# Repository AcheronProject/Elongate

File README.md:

# Acheron 50-SM-S-F072-MX-TH-WI (Codename "Elongate")

See [this page](https://gondolindrim.github.io/AcheronDocs/elongate/intro.html) for the ElongatePCB documentation.

## Supported layouts

Click [this link](http://www.keyboard-layout-editor.com/#/gists/a7ea70bf0b0dbade28f4dd3f8dd61796) for the KLE file for Elongate.

## Renders

Click at the images to zoom in.

Renders generated by the [tracespace.io](https://tracespace.io/view/) site.

## Copyright notice

This project is released under the Acheron Open-Hardware License V1.3. For the license, please refer to the LICENCE.md file.

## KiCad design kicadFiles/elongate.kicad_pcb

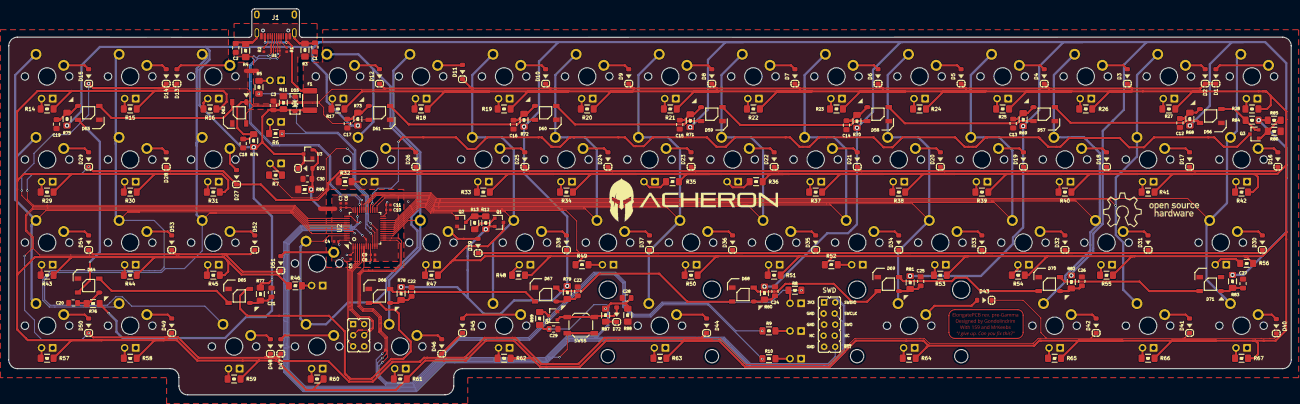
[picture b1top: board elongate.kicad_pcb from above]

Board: 2 copper layers, 294.0 x 88.5 mm, 324 parts (1 on the bottom side), 198 nets.

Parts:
C1, C2: 100n; C_0805_2012Metric_Pad1.15x1.40mm_HandSolder
C3, C12, C13, C14, C15, C16, C17, C18, C19, C20, C21, C22, C23, C24, C25, C26, C27, C30: 1u; C_0805_2012Metric_Pad1.15x1.40mm_HandSolder
C4, C5, C6, C10: 100n; C_0402_1005Metric
C7, C11: 4.7u; C_0402_1005Metric
C8: 1u; C_0402_1005Metric
C9: 10n; C_0402_1005Metric
C28: 100u; C_0805_2012Metric_Pad1.15x1.40mm_HandSolder
C29: 10u; C_0805_2012Metric_Pad1.15x1.40mm_HandSolder
D1, D2, D3, D4, D5, D6, D7, D8, D9, D10, D11, D12, D13, D14, D15, D16, D17, D18, D19, D20, D21, D22, D23, D24, D25, D26, D27, D28, D29, D30, D31, D32, D33, D34, D35, D36, D37, D38, D39, D40, D41, D42, D43, D44, D45, D46, D47, D48, D49, D50, D51, D52, D53, D54, D72: 1N4148; D_SOD-123
D55: SMF9.0CA; D_SOD-123_Bidirectional
D56, D57, D58, D59, D60, D61, D62, D63, D64, D65, D66, D67, D68, D69, D70, D71: WS2812C; LED_WS2812B_5.0x5.0mm_P3.2mm
D73: RB060M-60TR; D_SOD-123
F1: RF1338-000; Fuse_1812_4532Metric_Pad1.30x3.40mm_HandSolder
J1: TYPE-C-31-M12_13; TYPE-C-31-M-12
J2: Conn_ARM_JTAG_SWD_10
J3: Conn_01x6; PinHeader_2x3_P2.54mm_Vertical
L1: AcheronLogo; acheronLong
L2: ElongateLogoPlated; elongateLogo
L3: ElongateLabel; elongateLabel
L4: OSHLogo; osh-logo
L5: BRFlag; brazilFlag
LED1, LED2, LED3, LED4, LED5, LED6, LED7, LED8, LED9, LED10, LED11, LED12, LED13, LED14, LED15, LED16, LED17, LED18, LED19, LED20, LED21, LED22, LED23, LED24, LED25, LED26, LED27, LED28, LED29, LED30, LED31, LED32, LED33, LED34, LED35, LED36, LED37, LED38, LED39, LED40, LED41, LED42, LED43, LED44, LED45, LED46, LED47, LED48, LED49, LED50, LED51, LED52, LED53, LED54, LED55, LED56, LED57, LED58, LED59, LED60: LED; LED_THT_2.54mm
Q1, Q3: AO3401A; SOT-23
Q2, Q4: DTC123JKAT146; SOT-23
R1, R2: 5.1k; R_0402_1005Metric
R3, R4: 1M; R_SMD_1206
R5, R6, R7, R8, R9, R10, R14, R15, R16, R17, R18, R19, R20, R21, R22, R23, R24, R25, R26, R27, R28, R29, R30, R31, R32, R33, R34, R35, R36, R37, R38, R39, R40, R41, R42, R43, R44, R45, R46, R47, R48, R49, R50, R51, R52, R53, R54, R55, R56, R57, R58, R59, R60, R61, R62, R63, R64, R65, R66, R67: 390R; R_SMD_1206
R11, R88, R90: 100k; R_SMD_1206
R12, R84, R86: 10k; R_SMD_1206
R13, R89: 100R; R_SMD_1206
R68, R69, R70, R71, R72, R73, R74, R75, R76, R77, R78, R79, R80, R81, R82, R83: 3R; R_SMD_1206
R85: 5.1k; R_SMD_1206
R87: 33k; R_SMD_1206
SW1, SW2, SW3, SW4, SW5, SW6, SW7, SW8, SW9, SW10, SW11, SW12, SW13, SW14, SW15, SW17, SW18, SW19, SW20, SW21, SW22, SW23, SW24, SW25, SW27, SW28, SW29, SW31, SW32, SW33, SW34, SW35, SW36, SW37, SW38, SW41, SW45, SW46, SW47, SW48, SW49, SW50, SW51, SW52, SW53, SW54: MXSwitch; MX100
SW16, SW39, SW40, SW42: MXSwitch; MX125
SW26, SW30: MXSwitch; MX175
SW43: MXSwitch; MX225R
SW44: MXSwitch; MX275R
SW55: K2-1187SQ-A4SW-06; smdPushBtn
U1: TPD4E05U06DQAR; USON-10_2.5x1.0mm_P0.5mm
U2: STM32F072CBT6; LQFP-48_7x7mm_P0.5mm
U3: MCP1700-3302E; SOT-23

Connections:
3V3: C4.2, C5.1, C6.1, C7.1, C8.2, C9.2, C10.1, C11.1, C30.2, D73.2 (A), J2.1 (VTref), J3.5, R90.1, SW55.1, U2.1 (VBAT), U2.9 (VDDA), U2.24 (VDD), U2.36 (VDDIO2), U2.48 (VDD), U3.2 (VO)
5V: C3.1, D55.2 (A2), D73.1 (K), F1.2, Q1.2 (S), R11.2, R12.1, R68.1, R69.1, R70.1, R71.1, R72.1, R73.1, R74.1, R75.1, R76.1, R77.1, R78.1, R79.1, R80.1, R81.1, R82.1, R83.1, R84.1, R85.1, U3.3 (VI)
/SHIELD: C1.1, C2.1, J1.S (SHIELD), R3.2, R4.2
BOOT0: C28.2, R87.1, R88.1, U2.44 (BOOT0)
Col1: SW1.1 (Col), SW16.1 (Col), SW30.1 (Col), SW40.1 (Col), U2.31 (TIM1_CH3/PA10)
Col2: SW2.1 (Col), SW17.1 (Col), SW41.1 (Col), U2.30 (TIM1_CH2/PA9)
Col3: SW3.1 (Col), SW18.1 (Col), SW31.1 (Col), SW42.1 (Col), U2.29 (TIM1_CH1/PA8)
Col4: SW4.1 (Col), SW19.1 (Col), SW32.1 (Col), U2.27 (PB14/SPI2_MISO/I2S2_MCK/I2C2_SDA/TIM15_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)
Col5: SW5.1 (Col), SW20.1 (Col), SW33.1 (Col), SW43.1 (Col), U2.25 (PB12)
Col6: SW6.1 (Col), SW21.1 (Col), SW34.1 (Col), U2.22 (PB11/TIM2_CH4/I2C2_SDA)
Col7: SW7.1 (Col), SW22.1 (Col), SW35.1 (Col), U2.21 (PB10/SPI2_SCK/I2C2_SCL/TIM2_CH3)
Col8: SW8.1 (Col), SW23.1 (Col), SW36.1 (Col), SW44.1 (Col), U2.20 (PB2)
Col9: SW9.1 (Col), SW24.1 (Col), SW37.1 (Col), U2.19 (PB1/TIM3_CH4/TIM14_CH1/ADC_IN9)
Col10: SW10.1 (Col), SW25.1 (Col), SW38.1 (Col), SW45.1 (Col), U2.17 (PA7/TIM3_CH2/TIM14_CH1/ADC_IN7)
Col11: SW11.1 (Col), SW39.1 (Col), SW46.1 (Col), U2.15 (PA5/ADC_IN5/DAC_OUT2)
Col12: SW12.1 (Col), SW26.1 (Col), SW47.1 (Col), SW51.1 (Col), U2.46 (SPI2_NSS/I2S2_WS/I2C1_SDA/TIM17_CH1/PB9)
Col13: SW13.1 (Col), SW27.1 (Col), SW48.1 (Col), SW52.1 (Col), U2.45 (I2C1_SCL/TIM16_CH1/PB8)
Col14: SW14.1 (Col), SW28.1 (Col), SW49.1 (Col), SW53.1 (Col), U2.43 (2C1_SDA/PB7)
Col15: SW15.1 (Col), SW29.1 (Col), SW50.1 (Col), SW54.1 (Col), U2.42 (I2C1_SCL/PB6)
D+: J1.A6 (D+), J1.B6 (D+), U1.2 (IO2), U1.5 (D2-), U1.6 (NC), U1.9 (NC), U2.33 (USB_DP/PA12)
D-: J1.A7 (D-), J1.B7 (D-), U1.1 (IO1), U1.4 (D2+), U1.7 (NC), U1.10 (NC), U2.32 (USB_DM/TIM1_CH4/PA11)
EXTRA_1: J3.1, U2.2 (PC13)
EXTRA_2: J3.2, U2.3 (PC14/OSC32_IN)
EXTRA_3: J3.3, U2.4 (PC15/OSC32_OUT)
EXTRA_4: J3.4, U2.5 (PF0/OSC_IN)
GND: C1.2, C2.2, C3.2, C4.1, C5.2, C6.2, C7.2, C8.1, C9.1, C10.2, C11.2, C12.2, C13.2, C14.2, C15.2, C16.2, C17.2, C18.2, C19.2, C20.2, C21.2, C22.2, C23.2, C24.2, C25.2, C26.2, C27.2, C28.1, C29.1, C30.1, D55.1 (A1), D56.3 (VSS), D57.3 (VSS), D58.3 (VSS), D59.3 (VSS), D60.3 (VSS), D61.3 (VSS), D62.3 (VSS), D63.3 (VSS), D64.3 (VSS), D65.3 (VSS), D66.3 (VSS), D67.3 (VSS), D68.3 (VSS), D69.3 (VSS), D70.3 (VSS), D71.3 (VSS), J1.A1 (GND), J1.B1 (GND), J2.3 (GND), J2.5 (GND), J2.9 (GNDDetect), J3.6, LED1.K, LED2.K, LED3.K, LED4.K, LED5.K, LED6.K, LED7.K, LED8.K, LED9.K, LED10.K, LED11.K, LED12.K, LED13.K, LED14.K, LED15.K, LED16.K, LED17.K, LED18.K, LED19.K, LED20.K, LED21.K, LED22.K, LED23.K, LED24.K, LED25.K, LED26.K, LED27.K, LED28.K, LED29.K, LED30.K, LED31.K, LED32.K, LED33.K, LED34.K, LED35.K, LED36.K, LED37.K, LED38.K, LED39.K, LED40.K, LED41.K, LED42.K, LED43.K, LED44.K, LED45.K, LED46.K, LED47.K, LED48.K, LED49.K, LED50.K, LED51.K, LED52.K, LED53.K, LED54.K, LED55.K, LED56.K, LED57.K, LED58.K, LED59.K, LED60.K, Q2.2 (E), Q4.2 (E), R1.1, R2.1, R3.1, R4.1, R11.1, R86.2, R88.2, R90.2, U1.3 (GND), U1.8 (GND), U2.8 (VSSA), U2.23 (VSS), U2.35 (VSS), U2.47 (VSS), U3.1 (GND)
INDICATOR1: R5.1, U2.12 (PA2/ADC_IN2)
INDICATOR2: R6.1, U2.11 (PA1/ADC_IN1)
INDICATOR3: R7.1, U2.10 (PA0/ADC_IN0)
INDICATOR4: R8.1, U2.14 (PA4/TIM14_CH1/ADC_IN4)
INDICATOR5: R9.1, U2.13 (PA3/TIM15_CH2/ADC_IN3)
INDICATOR6: R10.1, U2.6 (PF1/OSC_OUT)
LED_PWM: Q2.1 (B), U2.16 (PA6/ADC_IN6/TIM3_CH1/TIM16_CH1)
unnamed: C12.1, D56.1 (VDD), R68.2
unnamed: C13.1, D57.1 (VDD), R69.2
unnamed: C14.1, D58.1 (VDD), R70.2
unnamed: C15.1, D59.1 (VDD), R71.2
unnamed: C16.1, D60.1 (VDD), R72.2
unnamed: C17.1, D61.1 (VDD), R73.2
unnamed: C18.1, D62.1 (VDD), R74.2
unnamed: C19.1, D63.1 (VDD), R75.2
unnamed: C20.1, D64.1 (VDD), R76.2
unnamed: C21.1, D65.1 (VDD), R77.2
unnamed: C22.1, D66.1 (VDD), R78.2
unnamed: C23.1, D67.1 (VDD), R79.2
unnamed: C24.1, D68.1 (VDD), R80.2
unnamed: C25.1, D69.1 (VDD), R81.2
unnamed: C26.1, D70.1 (VDD), R82.2
unnamed: C27.1, D71.1 (VDD), R83.2
unnamed: D1.2 (A), SW1.2 (Row)
unnamed: D2.2 (A), SW2.2 (Row)
unnamed: D3.2 (A), SW3.2 (Row)
unnamed: D4.2 (A), SW4.2 (Row)
unnamed: D5.2 (A), SW5.2 (Row)
unnamed: D6.2 (A), SW6.2 (Row)
unnamed: D7.2 (A), SW7.2 (Row)
unnamed: D8.2 (A), SW8.2 (Row)
unnamed: D9.2 (A), SW9.2 (Row)
unnamed: D10.2 (A), SW10.2 (Row)
unnamed: D11.2 (A), SW11.2 (Row)
unnamed: D12.2 (A), SW12.2 (Row)
unnamed: D13.2 (A), SW13.2 (Row)
unnamed: D14.2 (A), SW14.2 (Row)
unnamed: D15.2 (A), SW15.2 (Row)
unnamed: D16.2 (A), SW16.2 (Row)
unnamed: D17.2 (A), SW17.2 (Row)
unnamed: D18.2 (A), SW18.2 (Row)
unnamed: D19.2 (A), SW19.2 (Row)
unnamed: D20.2 (A), SW20.2 (Row)
unnamed: D21.2 (A), SW21.2 (Row)
unnamed: D22.2 (A), SW22.2 (Row)
unnamed: D23.2 (A), SW23.2 (Row)
unnamed: D24.2 (A), SW24.2 (Row)
unnamed: D25.2 (A), SW25.2 (Row)
unnamed: D26.2 (A), SW26.2 (Row)
unnamed: D27.2 (A), SW27.2 (Row)
unnamed: D28.2 (A), SW28.2 (Row)
unnamed: D29.2 (A), SW29.2 (Row)
unnamed: D30.2 (A), SW30.2 (Row)
unnamed: D31.2 (A), SW31.2 (Row)
unnamed: D32.2 (A), SW32.2 (Row)
unnamed: D33.2 (A), SW33.2 (Row)
unnamed: D34.2 (A), SW34.2 (Row)
unnamed: D35.2 (A), SW35.2 (Row)
unnamed: D36.2 (A), SW36.2 (Row)
unnamed: D37.2 (A), SW37.2 (Row)
unnamed: D38.2 (A), SW38.2 (Row)
unnamed: D39.2 (A), SW39.2 (Row)
unnamed: D40.2 (A), SW40.2 (Row)
unnamed: D41.2 (A), SW41.2 (Row)
unnamed: D42.2 (A), SW42.2 (Row)
unnamed: D43.2 (A), SW43.2 (Row)
unnamed: D44.2 (A), SW44.2 (Row)
unnamed: D45.2 (A), SW45.2 (Row)
unnamed: D46.2 (A), SW46.2 (Row)
unnamed: D47.2 (A), SW47.2 (Row)
unnamed: D48.2 (A), SW48.2 (Row)
unnamed: D49.2 (A), SW49.2 (Row)
unnamed: D50.2 (A), SW50.2 (Row)
unnamed: D51.2 (A), SW51.2 (Row)
unnamed: D52.2 (A), SW52.2 (Row)
unnamed: D53.2 (A), SW53.2 (Row)
unnamed: D54.2 (A), SW54.2 (Row)
unnamed: D56.2 (DOUT), D57.4 (DIN)
unnamed: D57.2 (DOUT), D58.4 (DIN)
unnamed: D58.2 (DOUT), D59.4 (DIN)
unnamed: D59.2 (DOUT), D60.4 (DIN)
unnamed: D60.2 (DOUT), D61.4 (DIN)
unnamed: D61.2 (DOUT), D62.4 (DIN)
unnamed: D62.2 (DOUT), D63.4 (DIN)
unnamed: D63.2 (DOUT), D64.4 (DIN)
unnamed: D64.2 (DOUT), D65.4 (DIN)
unnamed: D65.2 (DOUT), D66.4 (DIN)
unnamed: D66.2 (DOUT), D67.4 (DIN)
unnamed: D67.2 (DOUT), D68.4 (DIN)
unnamed: D68.2 (DOUT), D69.4 (DIN)
unnamed: D69.2 (DOUT), D70.4 (DIN)
unnamed: D70.2 (DOUT), D71.4 (DIN)
unnamed: D72.1 (K), R87.2
unnamed: D72.2 (A), Q4.1 (B), SW55.2
unnamed: J1.A5 (CC1), R1.2
unnamed: J1.B5 (CC2), R2.2
unnamed: LED1.A, R5.2
unnamed: LED2.A, R6.2
unnamed: LED3.A, R7.2
unnamed: LED4.A, R8.2
unnamed: LED5.A, R9.2
unnamed: LED6.A, R10.2
unnamed: LED7.A, R14.2
unnamed: LED8.A, R15.2
unnamed: LED9.A, R16.2
unnamed: LED10.A, R17.2
unnamed: LED11.A, R18.2
unnamed: LED12.A, R19.2
unnamed: LED13.A, R20.2
unnamed: LED14.A, R21.2
unnamed: LED15.A, R22.2
unnamed: LED16.A, R23.2
unnamed: LED17.A, R24.2
unnamed: LED18.A, R25.2
unnamed: LED19.A, R26.2
unnamed: LED20.A, R27.2
unnamed: LED21.A, R28.2
unnamed: LED22.A, R29.2
unnamed: LED23.A, R30.2
unnamed: LED24.A, R31.2
unnamed: LED25.A, R32.2
unnamed: LED26.A, R33.2
unnamed: LED27.A, R34.2
unnamed: LED28.A, R35.2
unnamed: LED29.A, R36.2
unnamed: LED30.A, R37.2
unnamed: LED31.A, R38.2
unnamed: LED32.A, R39.2
unnamed: LED33.A, R40.2
unnamed: LED34.A, R41.2
unnamed: LED35.A, R42.2
unnamed: LED36.A, R43.2
unnamed: LED37.A, R44.2
unnamed: LED38.A, R45.2
unnamed: LED39.A, R46.2
unnamed: LED40.A, R47.2
unnamed: LED41.A, R48.2
unnamed: LED42.A, R49.2
unnamed: LED43.A, R50.2
unnamed: LED44.A, R51.2
unnamed: LED45.A, R52.2
unnamed: LED46.A, R53.2
unnamed: LED47.A, R54.2
unnamed: LED48.A, R55.2
unnamed: LED49.A, R56.2
unnamed: LED50.A, R57.2
unnamed: LED51.A, R58.2
unnamed: LED52.A, R59.2
unnamed: LED53.A, R60.2
unnamed: LED54.A, R61.2
unnamed: LED55.A, R62.2
unnamed: LED56.A, R63.2
unnamed: LED57.A, R64.2
unnamed: LED58.A, R65.2
unnamed: LED59.A, R66.2
unnamed: LED60.A, R67.2
unnamed: Q1.1 (G), R13.1
unnamed: Q1.3 (D), R14.1, R15.1, R16.1, R17.1, R18.1, R19.1, R20.1, R21.1, R22.1, R23.1, R24.1, R25.1, R26.1, R27.1, R28.1, R29.1, R30.1, R31.1, R32.1, R33.1, R34.1, R35.1, R36.1, R37.1, R38.1, R39.1, R40.1, R41.1, R42.1, R43.1, R44.1, R45.1, R46.1, R47.1, R48.1, R49.1, R50.1, R51.1, R52.1, R53.1, R54.1, R55.1, R56.1, R57.1, R58.1, R59.1, R60.1, R61.1, R62.1, R63.1, R64.1, R65.1, R66.1, R67.1
unnamed: Q2.3 (C), R12.2, R13.2
unnamed: Q3.1 (G), R85.2, R86.1
unnamed: Q4.3 (C), R89.2
RGB_3V3: Q3.3 (D), U2.28 (SPI2_MOSI/I2S2_SD/PB15)
RGB_5V: D56.4 (DIN), Q3.2 (S), R84.2
Row1: D1.1 (K), D2.1 (K), D3.1 (K), D4.1 (K), D5.1 (K), D6.1 (K), D7.1 (K), D8.1 (K), D9.1 (K), D10.1 (K), D11.1 (K), D12.1 (K), D13.1 (K), D14.1 (K), D15.1 (K), U2.39 (SPI1_SCK/I2S1_CK/TIM2_CH2/PB3)
Row2: D16.1 (K), D17.1 (K), D18.1 (K), D19.1 (K), D20.1 (K), D21.1 (K), D22.1 (K), D23.1 (K), D24.1 (K), D25.1 (K), D26.1 (K), D27.1 (K), D28.1 (K), D29.1 (K), U2.38 (PA2)
Row3: D30.1 (K), D31.1 (K), D32.1 (K), D33.1 (K), D34.1 (K), D35.1 (K), D36.1 (K), D37.1 (K), D38.1 (K), D39.1 (K), U2.18 (PB0/TIM3_CH3/ADC_IN8)
Row4: D40.1 (K), D41.1 (K), D42.1 (K), D43.1 (K), D44.1 (K), D45.1 (K), D46.1 (K), D47.1 (K), D48.1 (K), D49.1 (K), D50.1 (K), U2.40 (SPI1_MISO/I2S1_MCK/TIM3_CH1/PB4)
Row5: D51.1 (K), D52.1 (K), D53.1 (K), D54.1 (K), U2.41 (SPI1_MOSI/I2S1_SD/TIM3_CH2/PB5)
SWCLK: J2.4 (SWDCLK/TCK), U2.37 (SWCLK/PA14)
SWDIO: J2.2 (SWDIO/TMS), U2.34 (SWDIO/PA13)
VBUS: F1.1, J1.A4 (VBUS), J1.B4 (VBUS)
nRST: C29.2, J2.10 (~RESET~), R89.1, U2.7 (NRST)

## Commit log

2019-07-10 [Update] Swapped all footprint to Acheron Library, finished schematic
2019-07-10 [Update] Finished placing components. Almost done routing. Logos still pending.
2019-07-11 [Update] Finished routing
2019-07-11 [Update] Added logos and label
2019-07-12 [Update] Updated gerbers, added plate gerber files
2019-07-23 Added DS_Store to gitignore
2019-08-26 feat: added script to parse BOM CSV
2019-08-27 Started mirroring PCB
2019-09-01 Breakout pins, refresh gerbers
2019-09-01 Added renders, LICENSE and README
2019-09-01 Fixed README renders paths
2019-09-01 Added schematic PDF
2019-09-01 Added BOM csv file
2019-09-11 Fix pins 34/35, optimized VCC routing
    - I dun goofed with the routing of pins 34 and 35, which are respectively VCC and GND, and they were routed the opposite way, which caused a short-circuit between VCC and GND, hindering be board bric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
    - There was a little optimization in the routing of the 5V net, specifically the trace going from the fuse. That trace was supposed to go trhough DF1, RF1 and CF1 and then to the MCU, when in reality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
    - A new schematic file was added to ./manuFiles/ folder
    - Gerbers were refreshed
2019-09-11 Refreshed schematic PDF file
2019-09-12 Added ISP header to schematic
2019-09-13 Expose ISP pins, rewire two cols
    - The ISP pins (PB1, PB2, PB3, RST, GND, VCC) were exposed ("broken out") so that ISP is more easily done;
    - Col 1 and col 2 were reassigned in the microcontroller for a better feeling
2019-09-13 Add RGB WS2812 LEDs to schematic
2019-09-13 Refresh gerbers and schematic PDF. Tag V1.2
2019-09-13 Refreshed schematic PDF
2019-09-15 Move label/logo files, put layout in README
    - The label and logo graphic files were placed inside a folder ./graphics/label_logo for better organization;
    - README file now contains supported layouts and the link for the KLE layout of Elongate
2019-09-15 [Fix] Fix README links
2019-10-28 Fix plate issues, final DRC run
2019-10-28 Update label to 'Revision Alpha'
2019-11-30 Add TVS, RGB, pi filter, new diodes and switches to the schematic
2019-11-30 Update Acheron Library submodule
2019-12-01 Finish routing, run DRC
2019-12-01 Update PCB file
2019-12-01 Update F.Fab layer
2019-12-01 Update renders
2019-12-01 Update README with plate render
2020-01-31 Pre-revision Beta release
2020-05-26 PCB global deletion and USBC connector port
2020-06-21 Change RCC resistors to R0402
2020-06-21 Added LEDs
2020-06-21 Finish LED placin, add MCU
2020-06-21 Almost finish routing, DRC pending
2020-06-23 Finish routing
2020-06-23 DRC ran, added indicators
2020-06-23 Solve symbol fields issues, prepare for pre-release Gamma
2020-06-23 Export pre-gamma files
2020-12-14 Added LICENSE
2020-12-14 Shortened USB lip to 10.2mm
2020-12-14 Solved level translator circuit issues
2020-12-14 Changed indicators as open-collector current sinks
2021-01-16 Remove reduntant files, remove AcheronLib submodule to update
2021-01-16 Added new Wurth USBC connector
2021-01-28 Change all silkscreen markings to 25/25/5 mil sizes
2021-01-28 Changed SWD for 6-pin equivalent
2021-01-29 Change LDO regulating caps to tantallums
2021-01-30 Add metadata to connector, move RCC resistors
2021-01-30 Preparing for release
2021-01-31 DRC ran, small corrections applied
2021-01-31 DRC ran, new label
2021-07-01 New gitignore
2021-07-01 Updated fills, DRC ran, erros corrected
2021-07-01 Updated component metatada
2023-02-05 fix errant D27 alignment
